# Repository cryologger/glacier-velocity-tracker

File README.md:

# Cryologger - Glacier Velocity Tracker (GVT)
### Note: This documentation is currently under development.

## 1.0 Introduction

Reliance on expensive and proprietary commercial data acquisition and telemetry systems can present a barrier to monitoring remote polar environments. The development of low-cost, open-source instrumentation can greatly reduce the cost of research in remote locations, improve the spatiotemporal resolution of collected data, and provide new ways to observe and monitor the cryosphere. 

The [Cryologger Glacier Velocity Tracker (GVT)](https://github.com/cryologger/glacier-velocity-tracker) is a novel [Cryologger](https://github.com/cryologger) design configuration intended to collect high temporal resolution velocity measurements to assess glacier dynamics on daily timescales in the Canadian Arctic. The system is based on the Arduino electronics platform and harnesses the u-blox ZED-F9P multi-frequency Global Navigation Satellite System (GNSS) receiver.

## 2.0 Methods

### 2.1 Design
The Cryologger GVT is based on the open-source Arduino platform (www.arduino.cc). Code is written using the Arduino Integrated Development Environment (IDE) and benefits from the availability of community-generated libraries.

The design of the Cryologger GVT takes into consideration several key principles, including cost-effectiveness, power efficiency, modularity, ruggedness, and ease of use. It is comprised of off-the-shelf components that do not require specialized tools or training, making it accessible to researchers, citizen scientists, and hobbyists alike. These selected components are also resistant to harsh environmental conditions, ensuring year-round continuous cold-weather operation.

#### 2.1.1 Bill of materials

The Cryologger GVT is built using almost exclusively using components from [SparkFun](https://www.sparkfun.com/), with a list of the main components shown below. For a more detailed bill of materials, including requirements for power and mounting of a complete deployable system, please see [ASSEMBLY.md](/Documentation/ASSEMBLY.md).

**Table 1.** Main components making up Cryologger GVT. Prices are listed in USD and are current as of December 2023. Taxes and shipping are not included.
| Component | Product | Quantity | Cost (USD) |
| --- | --- | :---: | :---: |
| PCB | [Custom Cryologger Printed Circuit Board](https://jlcpcb.com) | 1 | $5.00 | 
| Processor | [SparkFun MicroMod Artemis Processor](https://www.sparkfun.com/products/16401) | 1 | $14.95 | 
| Carrier Board | [SparkFun MicroMod Data Logging Carrier Board](https://www.sparkfun.com/products/16829) | 1 | $21.50 | 
| GNSS Receiver | [SparkFun GPS-RTK-SMA Breakout - ZED-F9P](https://www.sparkfun.com/products/16481) | 1 | $274.95 | 
| GNSS Antenna | [SparkFun GNSS Multi-Band L1/L2 Surveying Antenna (TNC) - TOP106](https://www.sparkfun.com/products/17751) | 1 | $133.95 | 
| Display | [SparkFun Qwiic OLED Display](https://www.sparkfun.com/products/17153) | 1 | $10.95 |
| Voltage Regulator | [Pololu 5V, 600mA Step-Down Voltage Regulator D36V6F5](https://www.pololu.com/product/3792) | 1 | $6.95 |

#### 2.1.2 Design Evolution 

A carrier board was designed to simplify assembly and deployment. It provides 5.08 mm, 2-pin screw terminals for wiring the battery connection, and a resistor divider to measure battery voltage.

<p align="center"><b>Figure 1.</b> Open-source carrier board design.</p>

#### 2.1.3 Mock-up
The Cryologger GVT was originally intended to be installed in a small electronics enclosure that is mounted in a larger enclosure for deployment outdoors.

<p align="center"><b>Figure 2.</b> Open-source carrier board design.</p>

### 2.2 Operation

When initially powered on, the Cryologger GVT will attempt to establish a GNSS fix and synchronize the real-time clock (RTC) of the MicroMod Artemis Processor for up to 5 minutes. Once the RTC is synchronized, the system will set an alarm to wake at the user-specified time and then enter a low-power deep sleep.  Nominally, the system will wake daily and log data from the u-blox GNSS receiver to a microSD card for a period of 3 hours. There are three different logging modes available to the end end-user, which can be tailored to the data collection requirements and available power capacity.

Versions 2.2.1 and above of the Cryologger GVT are equipped with an OLED display. This display is used to provide detailed information to the end user about the status of the Cryologger at each stage of operation, including boot-up, initialization of components, acquisition of GNSS fix, and logging of data. 

In addition to the OLED display messages, a series of LED blink patterns can also be used to indicate system operation and guide possible troubleshooting steps that should be attempted if any errors is encountered. A detailed table of the LED blink patterns can be found in the [DEPLOYMENT.md](/Documentation/DEPLOYMET.md) documentation. 

While the system is in deep sleep, a Watchdog Timer (WDT) will wake the system to check the program has not frozen every 10 seconds and perform a reset, if necessary. This helps to ensure the long-term reliability of the system.

### 2.3 Data Processing

Data is logged in u-blox's proprietary .ubx format. Log files can be converted to RINEX using RTKLIB or Emlid Studio and submitted to NRCan's Precise Point Positioning (PPP) tool: https://webapp.geod.nrcan.gc.ca/geod/tools-outils/ppp.php

For a more detailed guide on the processing of data, please see "[PROCESSING.md](/Documentation/PROCESSING.md).

## 3.0 Deployments

Between 2021 and 2023, a total of 28 Cryologger GVT deployments were made by several different academic institutions, including the Univerity of Ottawa, Carleton University, University of Waterloo (Canada), Carnegie Mellon University (United States), and University of Fribourg (Switzerland). These deployments were made on glaciers in several geographically distinct locations, including Canada, the United States and Kyrgyzstan. Two case studies of deployments made by the University of Ottawa and the University of Waterloo on glaciers in the Yukon and Nunvaut, Canada are explored in more detail below.

<p align="left"><b>Figure 3.</b> Map of Cryologger GVT deployments made between 2021 and 2023.</p>

### 3.1 Lowell Glacier, Yukon, Canada

<p align="left"><b>Figure 4.</b> Map of Cryologger GVT deployments made in 2021 on the Lowell Glacier, Yukon.</p>

### 3.2 Belcher Glacier, Devon Island, Nunavut, Canada

<p align="left"><b>Figure 5.</b> Map of Cryologger GVT deployments made in 2021 on the Lowell Glacier, Yukon and Belcher Glacier, Devon Island, Nunavut.</p>

<p align="center">&nbsp;&nbsp;</p>
<p align="left"><b>Figure 6.</b> Deployment of the "Belcher Lower" Cryologger GVT on the Belcher Glacier, Devon Island, Nunavut.</p>

## 4.0 Results

Preliminary results from the 2021 deployments of Cryologger GVTs on Lowell Glacier, Kluane National Park, Yukon and Belcher Glacier, Devon Island, Nunavut are presented below.

### 4.1 Lowell Glacier, Yukon, Canada

The initial Cryologger GVTs deployments on Lowell Glacier were both successful, achieving continuous operation throughout the year. 

Collected data that was PPP-processed revealed the GVTs deployed on Lowell Glacier were able to achieve daily position measurements with accuracies of <3 cm. Daily displacements ranged between 0.25 – 4.4 m d<sup>-1</sup> and annual cumulative distances were between 200 – 700 m y<sup>-1</sup>. Both systems showed evidence of ongoing glacier surge cycles and excitingly were also able to capture periods of marked glacier velocity corresponding to local rainfall events and enhanced basal sliding.

<p align="left"><b>Figure 7.</b> Cumulative distance and daily displacement of Lowell Glacier, Yukon recorded between between 2021 and 2022.</p>

### 4.2 Belcher Glacier, Devon Island, Nunavut, Canada

Cryologger GVT deployments made on Belcher Glacier were also able to achieve successful operation throughout the entire year. The data collected between 2021-2022 represents the first uninterrupted annual velocity record of the Belcher Glacier ever recorded.

PPP-processed data showed the GVTs deployed on Belcher Glacier were also able to achieve daily position measurements with accuracies of <3 cm. Daily displacements ranged between 0.18 – 0.45 m d<sup>-1</sup> and annual cumulative distances were between 75 – 150 m y<sup>-1</sup>. These results are also in agreement with velocities derived from synthetic-aperture radar (SAR) remote sensing data.

<p align="left"><b>Figure 8.</b> Cumulative distance and daily displacement of Belcher Glacier, Devon Island recorded between between 2021 and 2022.</p>

## 5.0 Conclusions

Cryologger GVT deployments have demonstrated they can achieve continuous year-round operation. Data processed with Precise Point Positioning techniques also reveals the systems can achieve daily position measurements with accuracies of <3 cm. These promising results demonstrate that open-source hardware and software can provide a reliable and cost-effective alternative to commercially available equipment for use in glaciological monitoring.

## Acknowledgements

This project would not have been possible without the designs, software and tutorials provided by the open-source community. A special thanks to the authors of and contributors to the [SparkFun u-blox GNSS Arduino Library](https://github.com/sparkfun/SparkFun_u-blox_GNSS_Arduino_Library).

## Repository Contents

* **/Documentation** - Assembly, deployment and troubleshooting guides, as well as information on components used and associated costs.

* **/Hardware** - KiCad PCB schematic and design files.

* **/Software** -  Arduino code and Python data analysis scripts.

## License Information
Cryologger code, firmware, and software is licensed under the GNU General Public License v3.0 (https://www.gnu.org/licenses/gpl-3.0.en.html). 

<p xmlns:cc="http://creativecommons.org/ns#" >Cryologger hardware is licensed under <a href="https://creativecommons.org/licenses/by-nc-sa/4.0/?ref=chooser-v1" target="_blank" rel="license noopener noreferrer" style="display:inline-block;">CC BY-NC-SA 4.0 </a></p>

Cheers,

**Adam Garbo**

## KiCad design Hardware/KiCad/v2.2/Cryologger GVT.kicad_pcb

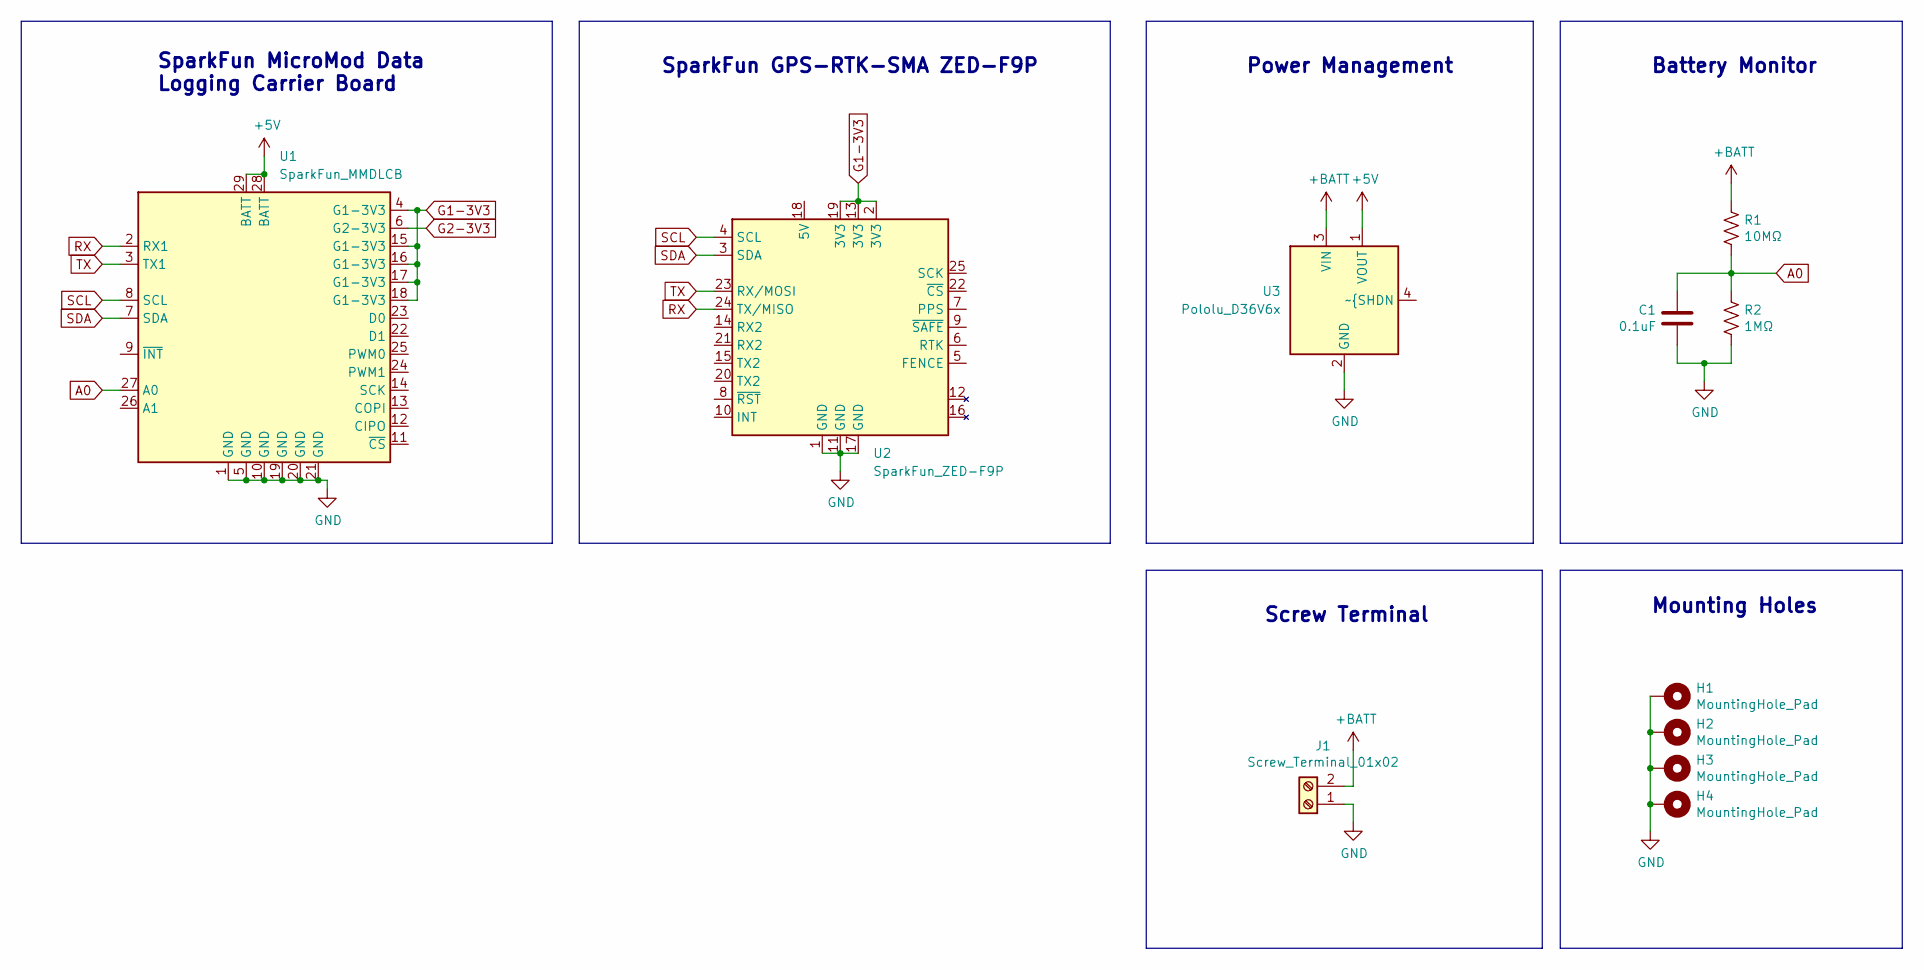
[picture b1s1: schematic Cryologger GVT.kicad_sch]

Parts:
C1: 0.1uF; C_Disc_D3.8mm_W2.6mm_P2.50mm
H1, H2, H3, H4: MountingHole_Pad; MountingHole_3.2mm_M3_Pad
J1: Screw_Terminal_01x02; TerminalBlock_Phoenix_MKDS-1,5-2-5.08_1x02_P5.08mm_Horizont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
R1: 10MΩ; R_Axial_DIN0207_L6.3mm_D2.5mm_P10.16mm_Horizontal
R2: 1MΩ; R_Axial_DIN0207_L6.3mm_D2.5mm_P10.16mm_Horizontal
U1: SparkFun_MMDLCB
U2: SparkFun_ZED-F9P
U3: Pololu_D36V6x; Pololu_D36V6x_Hor

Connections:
+5V: U1.28 (BATT), U1.29 (BATT), U3.1 (VOUT)
+BATT: J1.2, R1.1, U3.3 (VIN)
A0: C1.1, R1.2, R2.1, U1.27 (A0)
G1-3V3: U1.4 (G1-3V3), U1.15 (G1-3V3), U1.16 (G1-3V3), U1.17 (G1-3V3), U1.18 (G1-3V3), U2.2 (3V3), U2.13 (3V3), U2.19 (3V3)
G2-3V3: U1.6 (G2-3V3)
GND: C1.2, H1.1, H2.1, H3.1, H4.1, J1.1, R2.2, U1.1 (GND), U1.5 (GND), U1.10 (GND), U1.19 (GND), U1.20 (GND), U1.21 (GND), U2.1 (GND), U2.11 (GND), U2.17 (GND), U3.2 (GND)
RX: U1.2 (RX1), U2.24 (TX/MISO)
SCL: U1.8 (SCL), U2.4 (SCL)
SDA: U1.7 (SDA), U2.3 (SDA)
TX: U1.3 (TX1), U2.23 (RX/MOSI)

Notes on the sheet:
Battery Monitor
Screw Terminal
SparkFun MicroMod Data Logging Carrier Board
Mounting Holes
Power Management
SparkFun GPS-RTK-SMA ZED-F9P

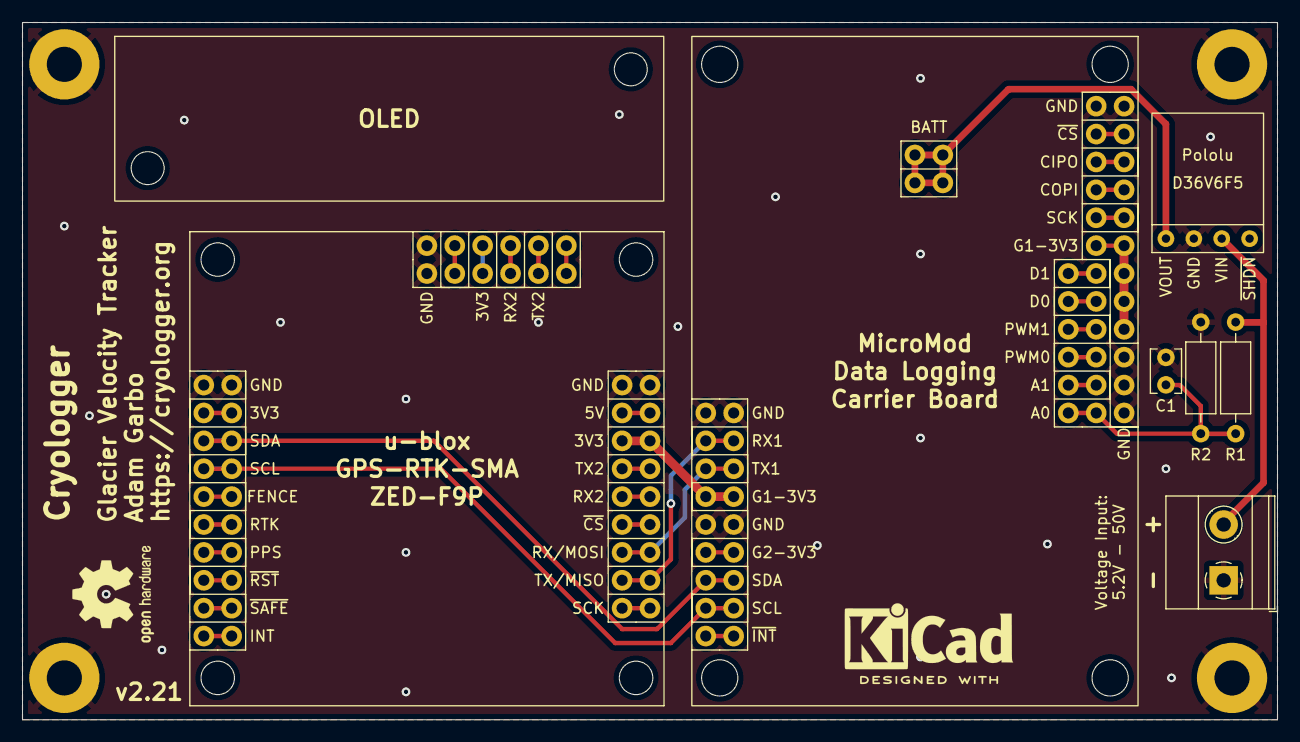
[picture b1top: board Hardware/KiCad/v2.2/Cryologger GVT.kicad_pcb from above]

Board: 2 copper layers, 114.3 x 63.5 mm, 11 parts (0 on the bottom side), 9 nets.

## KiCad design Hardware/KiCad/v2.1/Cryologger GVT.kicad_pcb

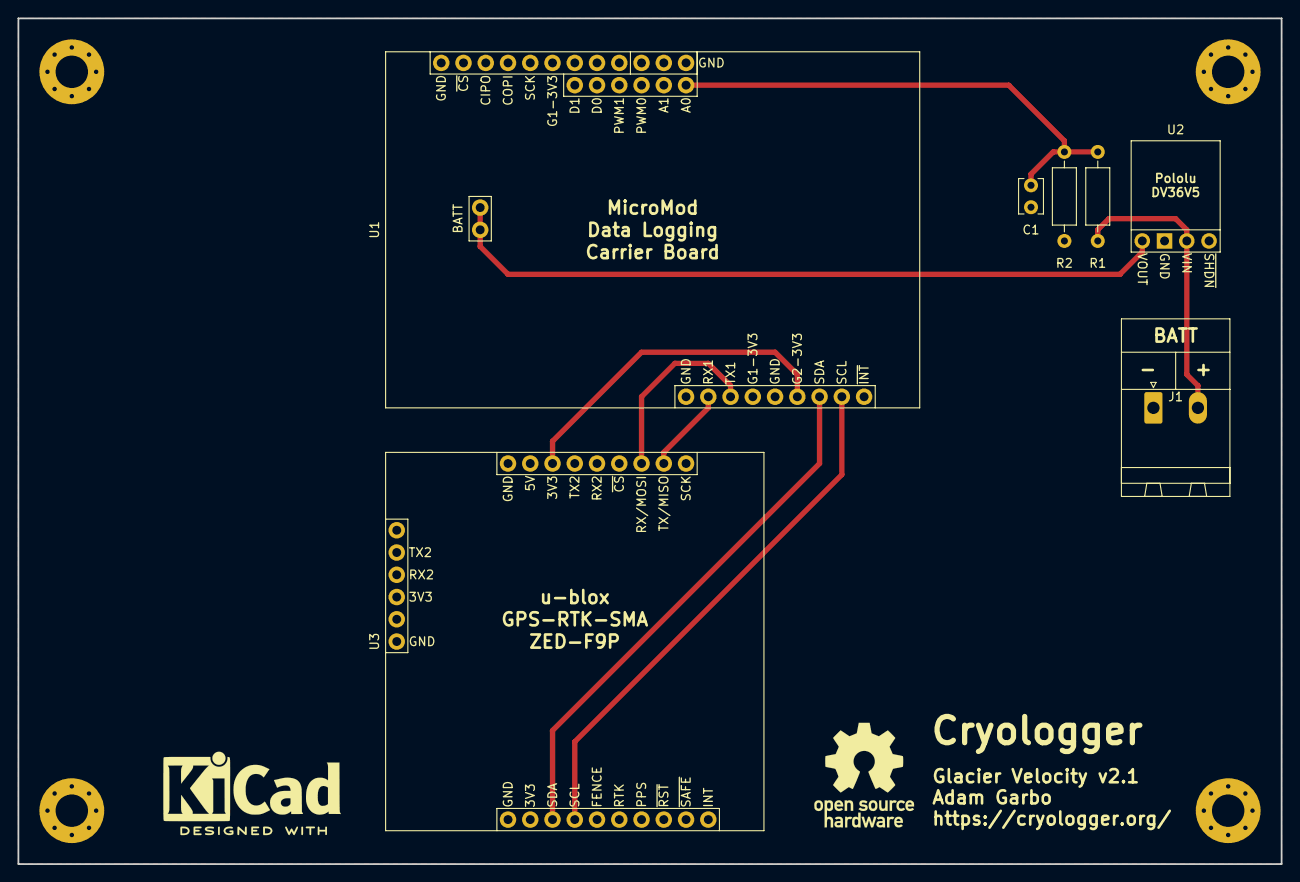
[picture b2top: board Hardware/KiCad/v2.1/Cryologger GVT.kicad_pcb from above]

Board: 2 copper layers, 144.2 x 96.5 mm, 11 parts (0 on the bottom side), 9 nets.

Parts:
C1: 0.1uF; C_Disc_D3.8mm_W2.6mm_P2.50mm
H1, H2, H3, H4: MountingHole_Pad; MountingHole_3.7mm_Pad_Via
J1: Screw_Terminal_01x02; PhoenixContact_MSTBA_2,5_2-G-5,08_1x02_P5.08mm_Horizontal
R1: 10MΩ; R_Axial_DIN0207_L6.3mm_D2.5mm_P10.16mm_Horizontal
R2: 1MΩ; R_Axial_DIN0207_L6.3mm_D2.5mm_P10.16mm_Horizontal
U1: MMDLCB; SparkFun_MMDLCB
U2: POLOLU_DV36; Pololu_D36V6
U3: GPS-RTK-SMA; SparkFun_GPS-RTK-SMA

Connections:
+3V3: U1.6, U3.19
+5V: U1.28, U1.29, U2.1
+BATT: J1.2, R1.1, U2.3
/A0: C1.1, R1.2, R2.1, U1.27
/RX: U1.3, U3.23
/SCL: U1.8, U3.4
/SDA: U1.7, U3.3
/TX: U1.2, U3.24
GND: C1.2, H1.1, H2.1, H3.1, H4.1, J1.1, R2.2, U1.1, U1.5, U1.19, U1.20, U1.21, U2.2, U3.1, U3.11, U3.17

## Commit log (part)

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2021-03-23 Remove Apollo3 Core v2.x modifications
2021-03-23 Update testing results
2021-03-24 Begin to add OLED code
2021-03-24 Add sleep option
2021-03-24 Modify low-power code
2021-03-25 Add debugging and disableUBX7Fcheck() functions
2021-03-26 Add specific alarm timings
2021-03-27 Add RTC drift calculation
2021-03-30 Add u-blox epoch time functionality
2021-03-30 Change RTC sync code to use getPVT instead of callbacks
2021-03-31 Remove OLED functionality
2021-04-01 Convert print statements to debug macros
2021-04-02 Consolidate MicroMod code versions
2021-04-02 Move log file name timestamping to separate function
2021-04-03 Add logging settings print function
2021-04-03 Add initialization failure reattempt code
2021-04-03 Remove OLA code
2021-04-03 Add logging mode, prepare for initial release
2021-04-04 Add additional debugging variables
2021-04-05 Disable Artemis internal pull-ups
2021-04-05 Begin to add conditional code for initialization failures
2021-04-06 Update version
2021-04-11 Rename software
2021-04-13 Minor update
2021-04-14 Add KiCad project files
2021-04-28 Troubleshooting u-blox initialization failures
2021-04-28 Fix u-blox power source functionality
2021-05-25 Re-enable control over Qwiic power
2021-06-22 Update KiCad files
2021-07-04 Improve blink pattern indicators
2021-07-04 Preparation of deployment code
2021-07-10 Fix GitHub library URL
2021-07-22 Add unique identifier to log and debug files
2021-12-08 Rename repository files
2022-03-13 Add updated KiCad files
2022-03-24 Add functionality to read battery voltage
    Configure system for testing prior to deployment
2022-03-27 Add support for OLED display
    Improve automatic logfile timestamp naming function
2022-03-27 Add 24-hour logging mode
    Minor WDT code comment improvements. Change read voltage function to return values. Add function to get time and print to buffer.
2022-03-29 Improve OLED code
    Add explicit control over internal pull-up resistors. Incorporate new reset function allowing OLED to recover from sleep/power cycles.
2022-03-29 Upload Gerber files
2022-03-29 Rename Gerber files
2022-03-30 Change delays to blocking for WDT reset
    Power down Qwiic connector and microSD when forcing a WDT reset.
2022-03-31 Move disabling pull-ups to before Wire.end()
    Make battery voltage analog reading global.
2022-03-31 Adjust delays
2022-03-31 Improve code commenting
2022-03-31 Remove setting of alarm flag causing false triggers
2022-04-04 Adjust gain and offset
    Values based on more in-depth characterization of resistor divider cirucit.
2022-04-04 Put OLED display to sleep after number of cycles
    Clean up RTC code. Add delay after RTC sync in order to be able to view drift value.
2022-04-04 Create LICENSE
2022-04-14 Update bill of materials
2022-04-24 Minor updates
2022-04-28 Added scheduled deep sleep mode
    Decreased WDT frequency.
2022-06-21 Remove scheduled sleep functionality
    Prepare code for future deployments on Ellesmere Island.
2022-06-21 Minor updates
    Improve log file naming. Rename tabs to standardized Cryologger names (i.e., logging, debug). Improve debug print statements.
2022-06-21 Adjust version number
2022-06-21 Adjust OLED display selection
2022-06-25 Hard code logging and sleep alarm modes based on operation
2022-06-25 Rename column header
2022-06-25 Add toggle code for OLED to prevent hanging
2022-06-25 Updates for deployment testing
2022-06-27 Update OLED display version
2022-06-27 Configure for continuous logging as default
2022-08-02 Improve OLED display messages
2022-08-03 Add missing constellation configuration options
2022-08-03 Rearrange order of microSD initialization
2022-08-04 Minor improvements to OLED display messages
2022-08-04 Minor updates
    Improved code commenting. Removal of LED blink patterns.
2022-08-04 Minor updates
    Improve unique identifier to include 3-letter abbreviation and unit number. Add additional OLED display messages.
2022-08-04 Update library versions
2022-08-15 Add PCB design revision v2.2
    Organize existing KiCad hardware and Gerber files. Create new global library symbols and footprints.
2022-08-23 Add OLED display reinitialization functionality
2022-08-23 Fix orientation of PCB OLED mounting holes
2022-08-23 Minor updates
    Prepare code for 2022 Lowell Glacier deployments. Create 3D PCB image.
2022-09-01 OLED display message improvements
2022-09-01 Revert "Update version"
    This reverts commit ccc04b14ab65624194f0727ee538848e1a4a9334.
2022-09-01 Update logging start and stop times for deployment
2022-12-05 Enable Galileo constellation
2023-03-17 Rename folders
    Removed old KiCad files.
2023-03-19 Organize folders
2023-03-28 Migrate code to SparkFun u-blox GNSS v3 library
2023-03-28 Update library version
2023-04-02 Migrate code to v3 method of querying u-blox registers
2023-04-02 Migrate code to SparkFun u-blox GNSS v3 library
    Standardized debug print statements. Removed code that would cause system to enter reset loop if component failure was encountered.
2023-04-02 Correct debug typos
2023-04-02 Configure code for testing
2023-04-08 Add 3D-printed solar panel drill guide files
2023-04-08 Add enclosure drill pattern files
2023-04-09 Adopt naming convention to make variable names more standardized/generic
2023-04-15 Add 3D-printing drill guide files
2023-04-28 Minor updates for v2.2 release
2023-04-29 Move documentation files
2023-04-29 Remove v1.0 archived files
2023-04-29 Organize and remove old KiCad files
2023-04-29 Configured for Arctic Bay deployments
2023-04-29 Update version number
2023-06-19 Add images for assembly documentation
2023-06-23 Set alarm modes from within alarm functions
    Added alarm hour and minute for daily logging mode. Updated corresponding debugging and display code.
2023-06-26 Major alarm improvements
    Integrated alarm modes directly into logging and sleep functions. Added minutes functionality to daily alarms. Updated relevant display and debugging code. Removed unnecessary return; commands.
2023-06-26 Minor GNSS updates
    Reverted GNSS timeout to seconds. Moved functions to appropriate tabs.
2023-06-26 Update cryologger_gvt.ino
    Updated variable names to consistent style. Improved daily and rolling alarm functionality. Added a daily check to sync RTC. Avoided unnecessary reinitialization of devices when in continuous mode. I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
2023-06-28 Correction to turn OLED display after specified period of time
2023-07-11 Upload documentation images
2023-07-11 Update image filename convention
    Added annotations to screenshots.
2023-07-11 Being updates to revert to Arduino IDE 1.8.x
2023-07-11 Rename file
2023-07-11 Continue revisions to revert to Arduino IDE v1.8.x
2023-07-12 Standardize image filenames
2023-07-12 Update image with identical file name
2023-08-07 Add documentation screenshots
2023-12-05 Remove G-Code
2024-01-12 Minor update to comments
2024-01-17 Include additional license information
2024-01-17 Add DOI badge
2024-03-11 Remove EAGLE files
2024-06-08 Fix typos
2024-09-19 Delete Documentation/SERVICING.md
    To be replaced by site-agnostic documentation.
2025-02-17 Add seasonal logging functionality
    Improved code commenting. Changed alarms to switch case. Adopted Clang 14.0.0 formatting. Added software and hardware versions. Changed unique identifier to serial number.
2025-02-17 Improve code commenting
    Adopted Clang 14.0.0 formatting.
2025-02-17 Improve microSD initialization logic
2025-02-17 Improve log file write and debug print logic
    Adopted serial number for log files.
2025-02-17 Add missing functions
2025-02-17 Improve efficiency of debug printing
2025-02-17 Add missing function
2025-02-17 Add new peripheral power restore function
2025-02-17 Major changes to summer logging mode
    Reworked code to gracefully enter and exit summer logging mode.
2025-02-17 Refinements to summer logging mode
2025-02-18 Apply Clang 14.0.0 formatting
2025-02-18 Refine summer mode logging
    Added debugging code to test all power-on scenarios.
2025-02-18 Improve code commenting
    Set test settings.
2025-02-21 Add check to close open debug file
2025-02-21 Seasonal logging mode improvements
    Changed naming convention to seasonal instead of summer logging mode. Eliminated initial alarm. Changed to day of year (DOY) approach for determining seasonal mode instead of MMDD.
2025-02-23 Improve code commenting
    Added GNSS firmware query to debugging.
2025-02-23 Add configuration from microSD card functionality
    System settings made configurable from JSON config file on microSD card.
2025-02-23 Add new user configuration section
    Improved code commenting. Changes related to new JSON config file located on microSD card.
2025-02-23 Make satellites configurable
    Added new variables to make satellites configurable from user section or JSON config file on microSD card.
2025-02-27 Add functionality to get microSD storage and file count
2025-03-05 Remove F() from Serial print statements
    Changed sprintf() specifiers to match variable types.
2025-03-05 Revert to simplified debug logging
    Removed Serial print statement from sleep function.
2025-03-05 Add GNSS and microSD display functions
2025-03-05 Move JSON config loading to setup
2025-03-06 Improve GNSS-related code
    Enhanced GNSS receiver initialization logic. Added configuration code to functions. Improved code commenting. No functional logging changes.
2025-03-08 Add missing checks for microSD online flag
2025-03-10 Add GNSS measurement rate to configuration file
2025-03-12 Improve JSON config file loading
    Enhanced variable validity checks.
2025-03-15 Add config.json file
2025-03-18 Remove F() from Serial print statements
2025-03-18 Use snprintf instead of sprintf to enforce bounds
    Applied Auto Format in Arduino 2.x to ensure proper formatting.
2025-03-18 Add JSON config OLED display message
    Changed approach for tracking validity of JSON configuration variables.
2025-03-18 Remove ArduinoJSON deprecated containsKey() calls and replace with doc["key"].is<T>()
    Changed displayInitialize() function to use const char *device.
2025-03-18 Add seasonal logging mode display message on OLED
2025-03-20 Address code commenting issues
2025-03-21 Increase RTC sync timeout period
    Decreased number of valid fixes required to sync RTC with GNSS.
2025-03-28 Default RTC sync GNSS measurement rate to 1 Hz
2025-03-28 Returned minimum fix counter to 10
2025-04-24 Update required libraries
2025-04-27 Remove Python files
2025-04-28 Change default measurement rate to 1 Hz
2025-06-12 Add additional OLED display screen
2025-06-12 Update software version
2025-06-13 Add boot display screen
    Adjusted spacing of GNSS info display screen.
2025-06-13 Update date
2025-06-15 Update badges
2025-07-03 Update libraries
2025-07-03 Fix CITATION.cff version to match tag v3.0.3
2025-07-04 Add link to CH340 drivers
2026-02-27 Update OLED display code
    Improved OLED initialization logic when the display was not physically connected but enabled in config. Added I2C device probing and improved pull-up stabilization timing.
2026-04-13 Update DOI badge
2026-04-16 Improve code comments.
2026-04-20 Update BoM
2026-04-26 Update code comments.
2026-04-26 Minor updates
    Improved logic to restore peripherals. Updated library versions. Improved comments.
2026-04-26 Update default config.json
    Disabled seasonal logging mode by default.
2026-04-28 Update bill of material pricing
2026-06-27 Minor OLED fix
2026-06-27 Improve code comments
2026-06-27 Reduce OLED display duration
2026-06-27 Update library versions and improve code comments
2026-06-27 Add functionality to track internal CPU temperature
2026-06-27 Add flag to enable immediate logging on first daily cycle
